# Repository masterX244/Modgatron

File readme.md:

Modification documentation for the upgrades of https://store.killerbody.com/products/killerbody-transformers-megatron-wearable-helmet-collectible-megatron-voice-changer for more fine-grained control.

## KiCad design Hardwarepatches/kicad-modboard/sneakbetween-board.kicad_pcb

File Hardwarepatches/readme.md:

Following patches were applied:

PCB traces to split:
    U1 Pin 18 to U6 Pin7
    U1 Pin 2 to U2 Pin 8

Wire to subboard to redirect:
    TODO: Recheck, wire from main to subboard which has connectivity to mouth servos
    
Wire to chip pin direct:
    one of: Pin 3 or 4 of U4 for injecting audio
    
Redirect switch board: see KICAD file

To Document: Lowpass circuitry and the switchover for custom audio using a CD4053b

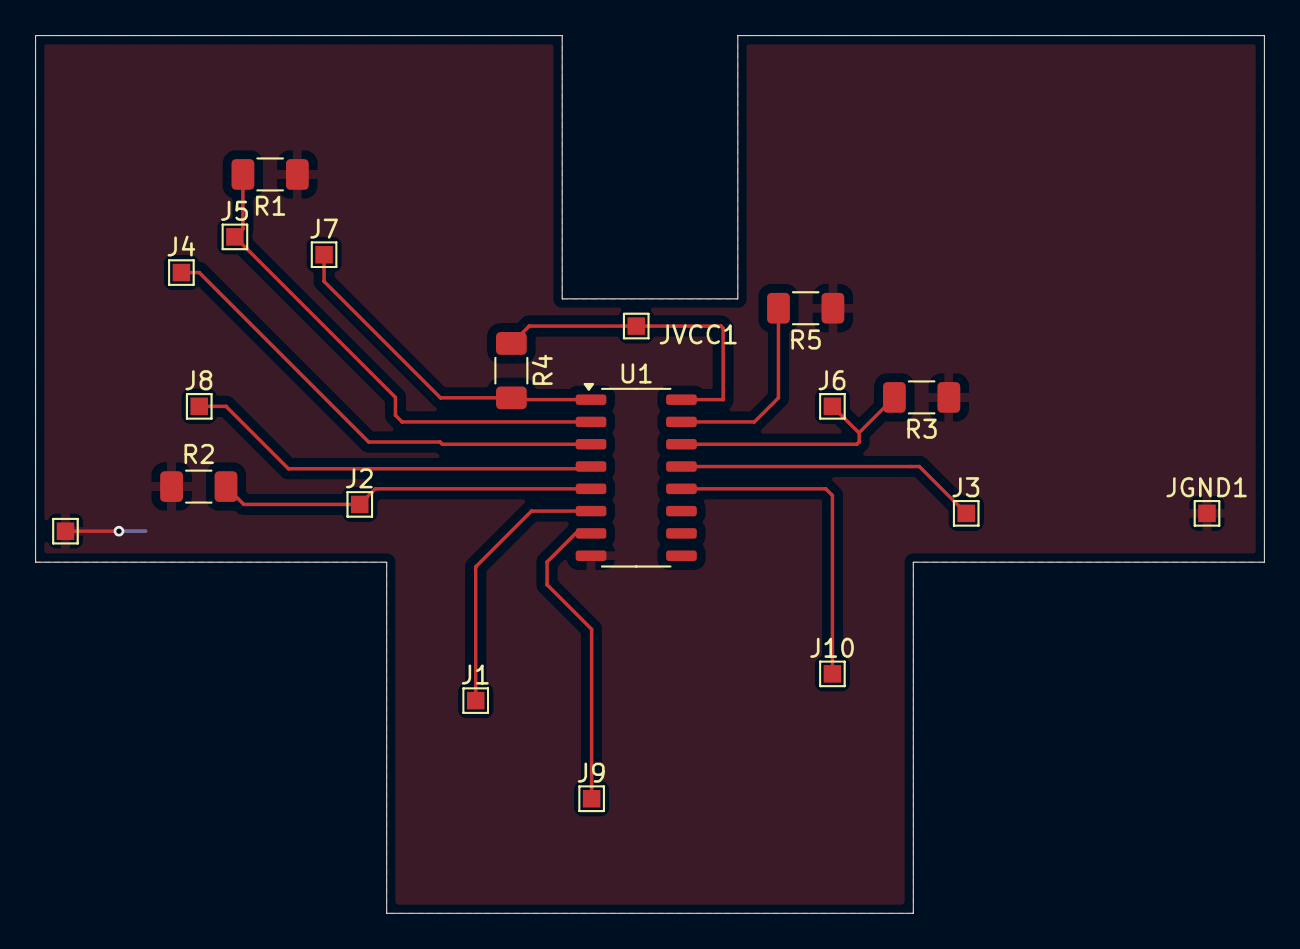
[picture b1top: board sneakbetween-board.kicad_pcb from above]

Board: 2 copper layers, 70.0 x 50.0 mm, 19 parts (0 on the bottom side), 13 nets.

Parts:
J1, J2, J3, J4, J5, J6, J7, J8, J9, J10: Conn_01x01_Pin; TestPoint_Pad_1.0x1.0mm
JGND1, JGND2: Conn_01x01_Pin; TestPoint_Pad_1.0x1.0mm
JVCC1: Conn_01x01_Pin; TestPoint_Pad_1.0x1.0mm
R1, R2, R3, R4, R5: 10K; R_1206_3216Metric_Pad1.30x1.75mm_HandSolder
U1: 74157; SO-16_3.9x9.9mm_P1.27mm

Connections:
+3.3V: JVCC1.1, R4.1, U1.16 (VCC)
GND: JGND1.1, JGND2.1, R1.1, R2.1, R3.1, R5.1, U1.8 (GND)
unnamed: J1.1, U1.6 (I1b)
unnamed: J2.1, R2.2, U1.5 (I0b)
unnamed: J3.1, U1.13 (I1c)
unnamed: J4.1, U1.3 (I1a)
unnamed: J5.1, R1.2, U1.2 (I0a)
unnamed: J6.1, R3.2, U1.14 (I0c)
unnamed: J7.1, R4.2, U1.1 (A/B)
unnamed: J8.1, U1.4 (Qa)
unnamed: J9.1, U1.7 (Qb)
unnamed: J10.1, U1.12 (Qc)
unnamed: R5.2, U1.15 (~EN)

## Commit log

2024-12-22 initial commit before 38C3
2024-12-22 one blocker preventing spring-boot fatjar from working fixed, one left unfortunately
2024-12-22 another stupid bug
